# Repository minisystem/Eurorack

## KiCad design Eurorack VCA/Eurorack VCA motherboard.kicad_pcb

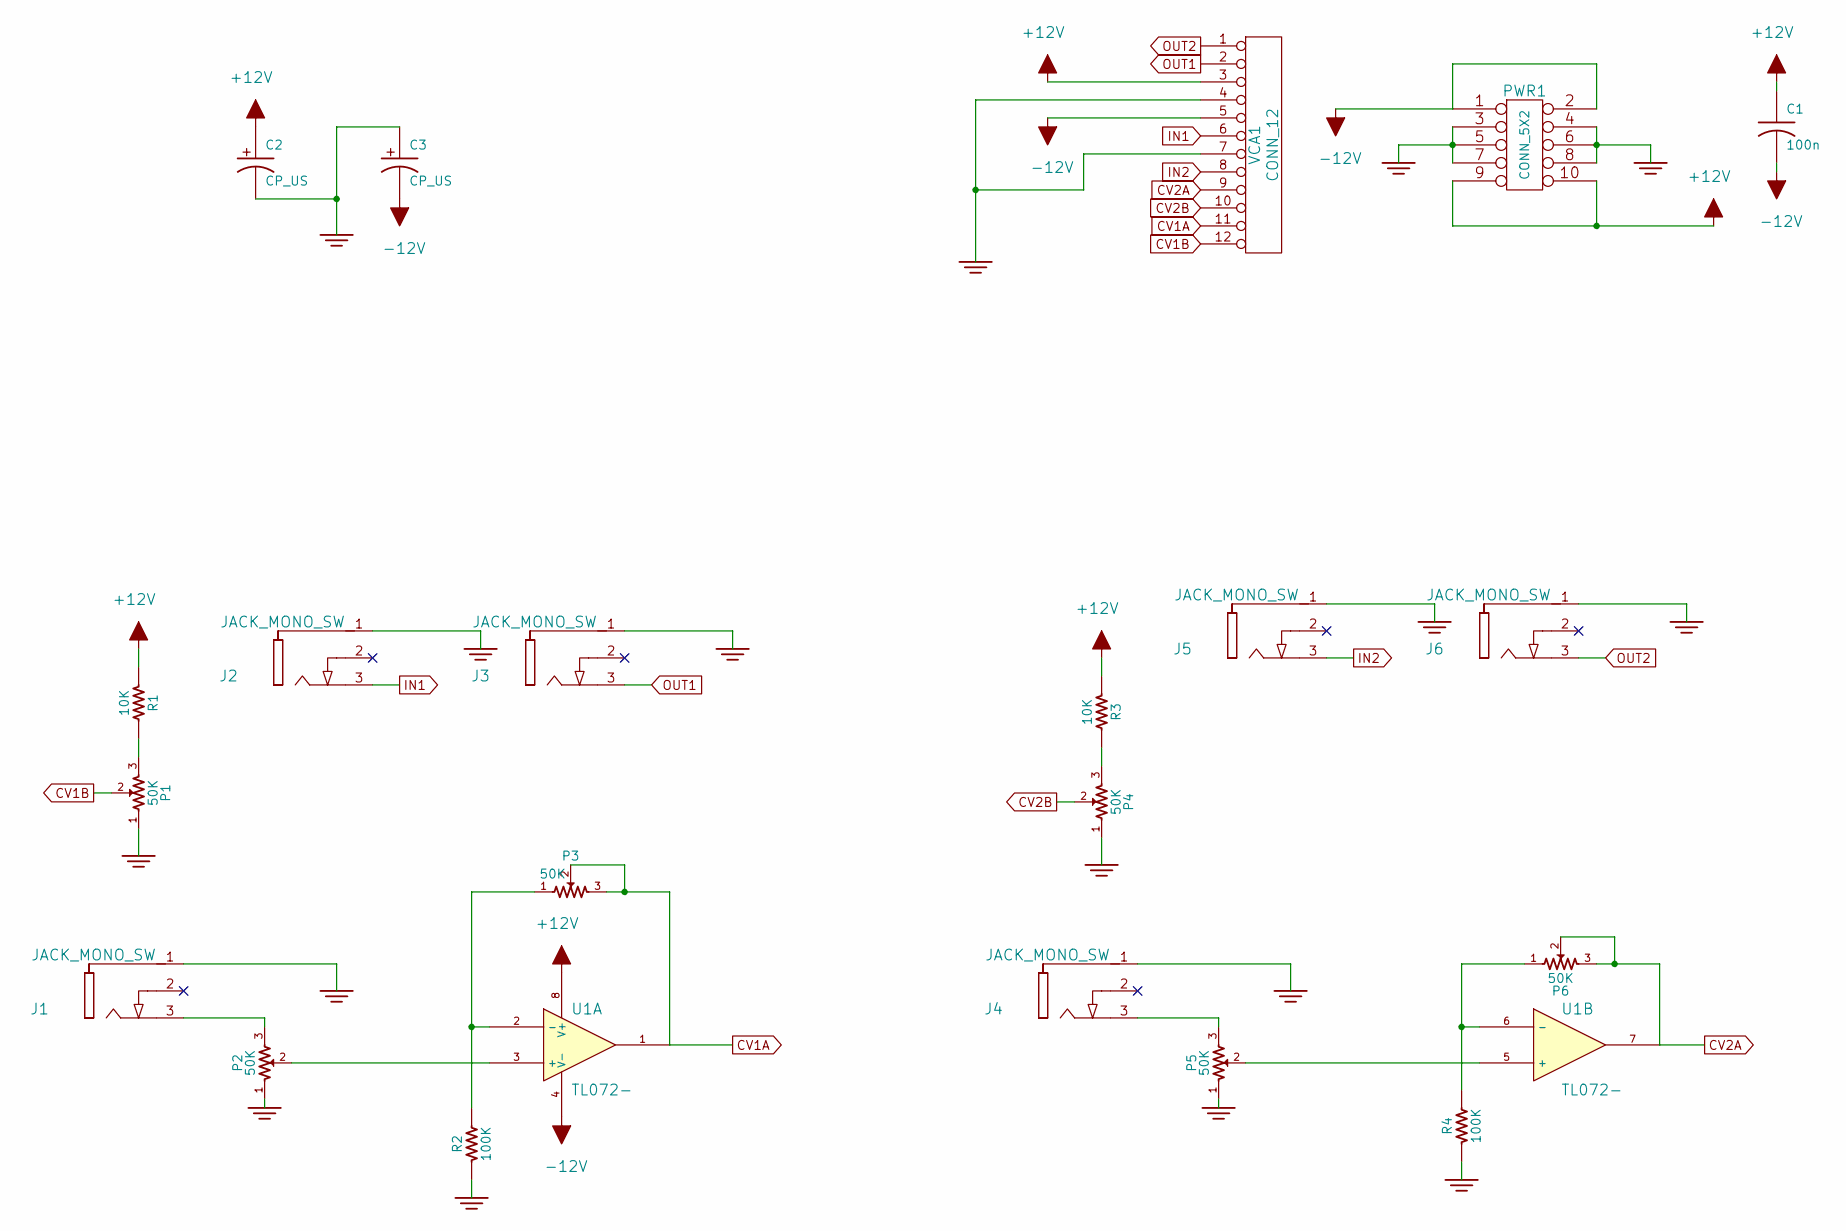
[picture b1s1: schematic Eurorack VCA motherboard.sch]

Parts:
C1: 100n
C2, C3: CP_US
J1, J2, J3, J4, J5, J6: JACK_MONO_SW
P1, P2, P3, P4, P5, P6: 50K
PWR1: CONN_5X2
R1, R3: 10K
R2, R4: 100K
U1: TL072-
VCA1: CONN_12

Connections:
+12V: C1.1, C2.1 (+), PWR1.9, PWR1.10, R1.1, R3.1, U1.8 (V+), VCA1.3
-12V: C1.2, C3.2 (-), PWR1.1, PWR1.2, U1.4 (V-), VCA1.5
CV1A: P3.2, P3.3, U1.1, VCA1.11
CV1B: P1.2, VCA1.12
CV2A: P6.2, P6.3, U1.7, VCA1.9
CV2B: P4.2, VCA1.10
GND: C2.2 (-), C3.1 (+), J1.1, J2.1, J3.1, J4.1, J5.1, J6.1, P1.1, P2.1, P4.1, P5.1, PWR1.3, PWR1.4, PWR1.5, PWR1.6, PWR1.7, PWR1.8, R2.1, R4.1, VCA1.4, VCA1.7
IN1: J2.3, VCA1.6
IN2: J5.3, VCA1.8
unnamed: J1.3, P2.3
unnamed: J4.3, P5.3
unnamed: P1.3, R1.2
unnamed: P2.2, U1.3 (+)
unnamed: P3.1, R2.2, U1.2 (-)
unnamed: P4.3, R3.2
unnamed: P5.2, U1.5 (+)
unnamed: P6.1, R4.2, U1.6 (-)
OUT1: J3.3, VCA1.2
OUT2: J6.3, VCA1.1

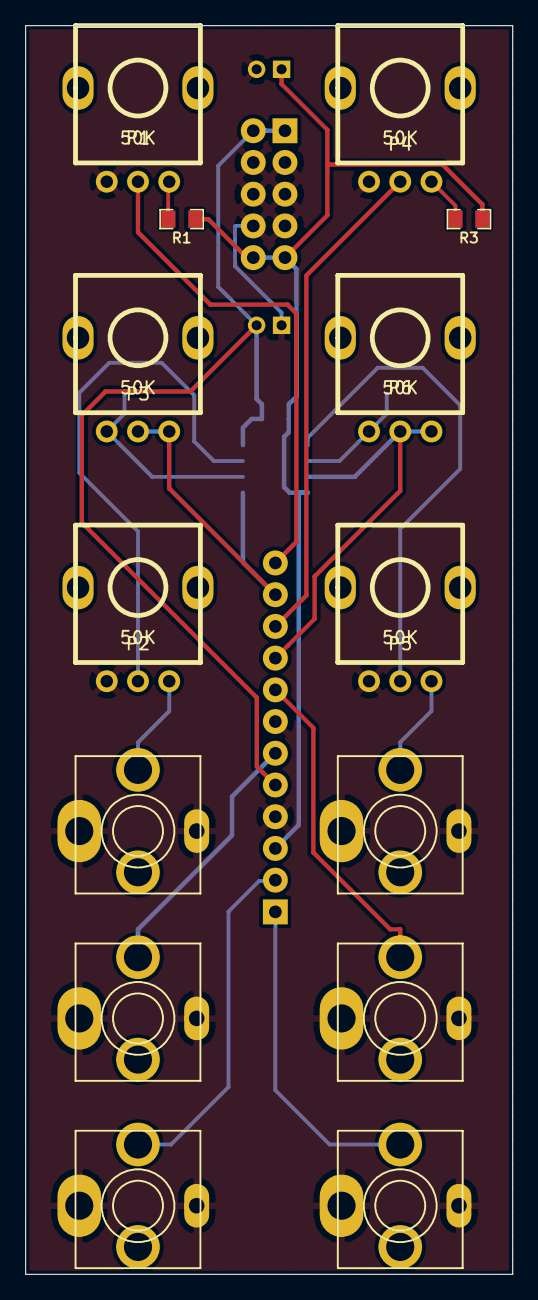
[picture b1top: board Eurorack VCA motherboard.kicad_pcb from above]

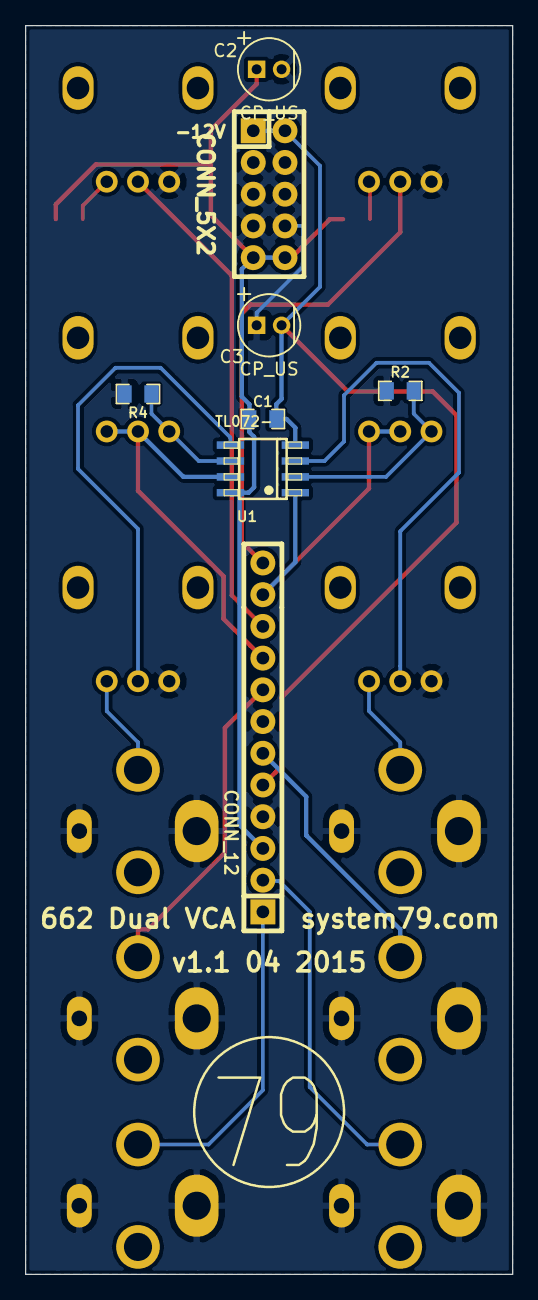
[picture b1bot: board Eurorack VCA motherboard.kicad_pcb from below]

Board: 2 copper layers, 39.0 x 100.0 mm, 23 parts (9 on the bottom side), 19 nets.

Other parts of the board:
system79-logo-12mm: VAL**; system79-logo-12mm

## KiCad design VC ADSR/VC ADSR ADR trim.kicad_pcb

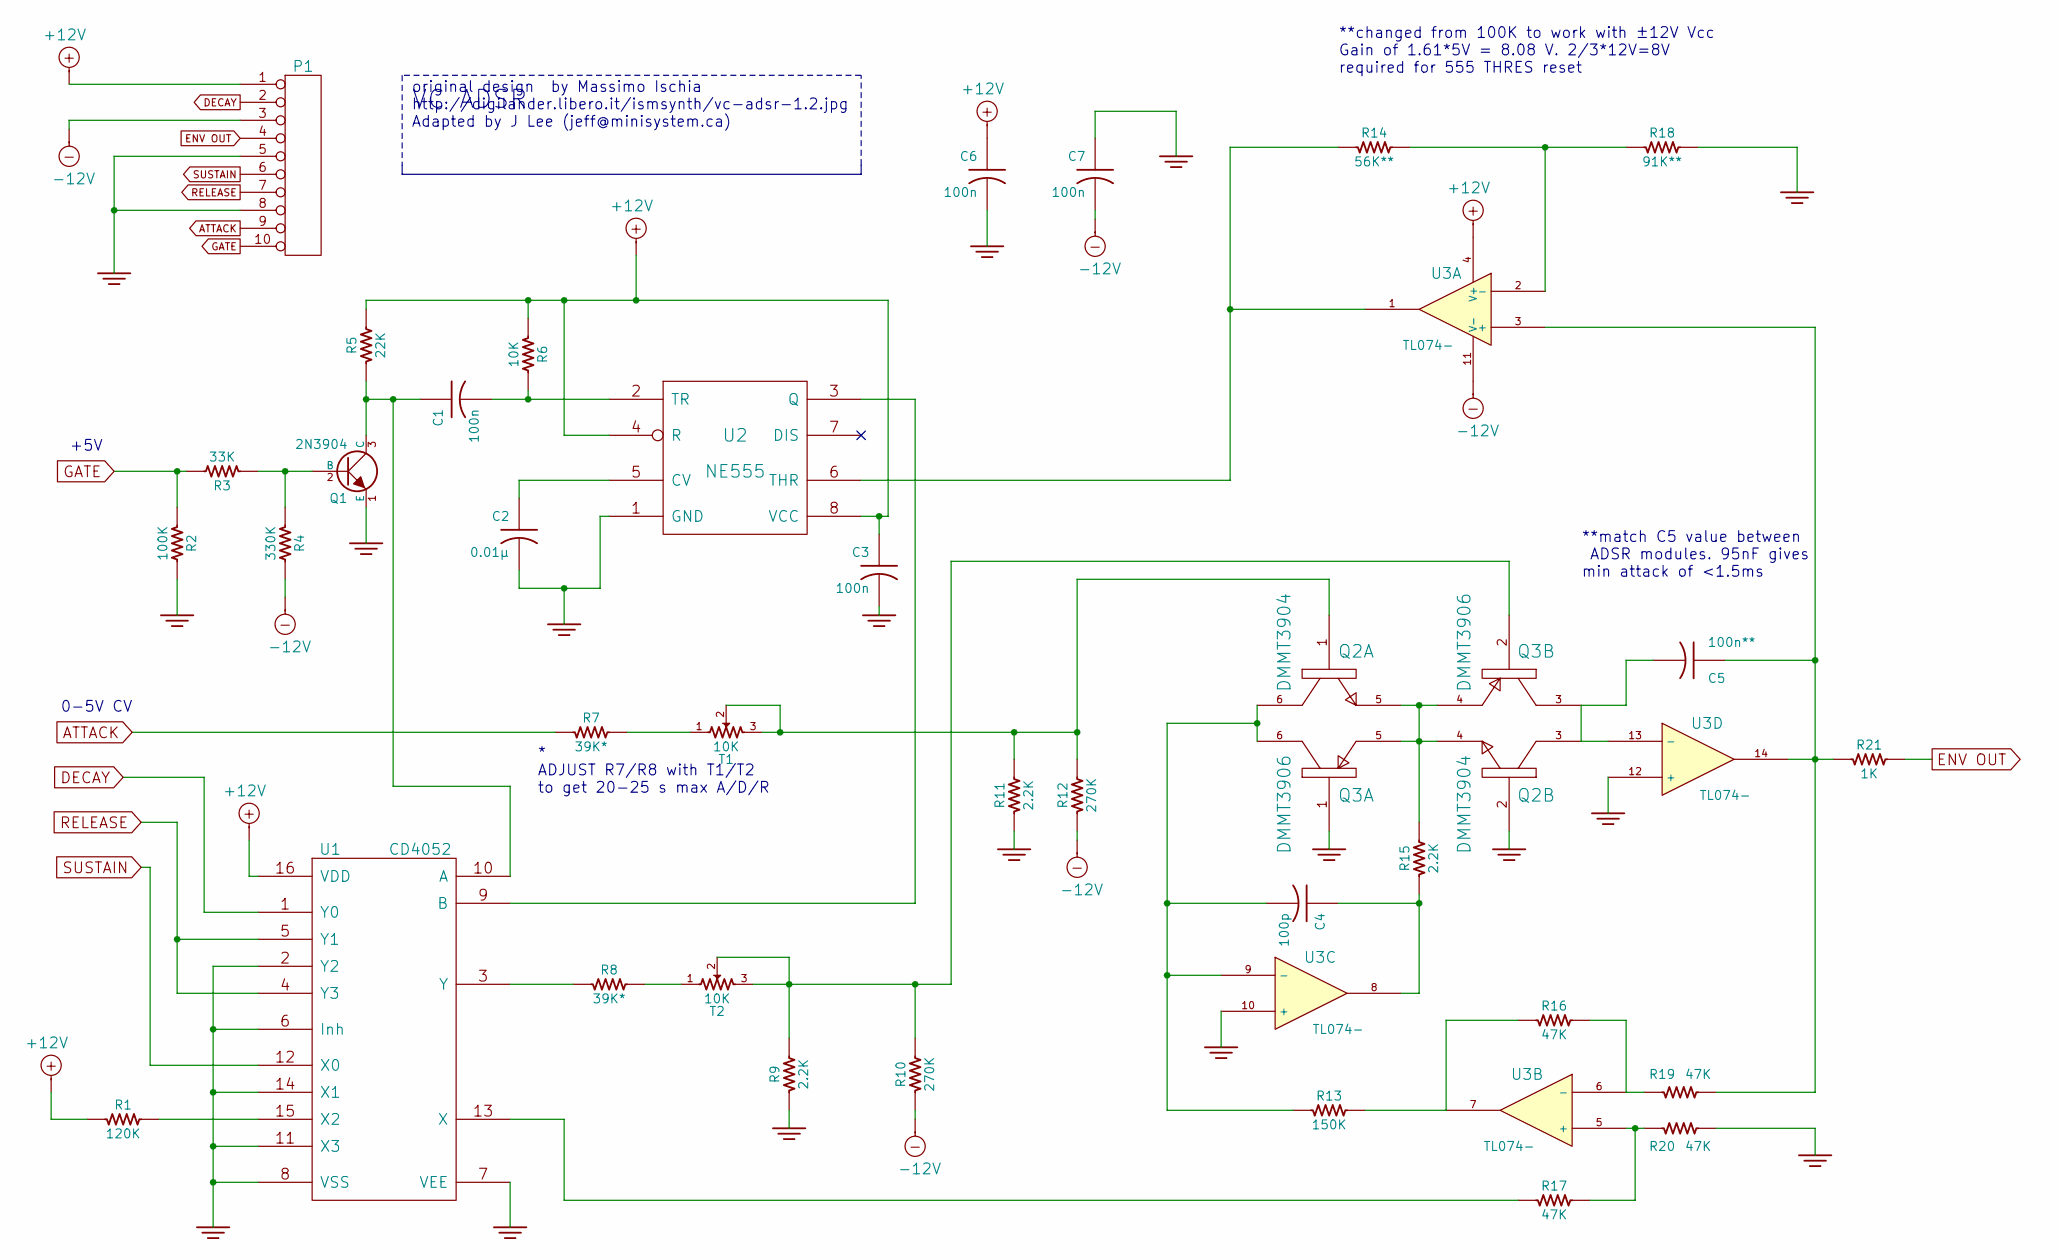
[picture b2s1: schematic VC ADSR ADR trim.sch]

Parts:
C1, C3, C6, C7: 100n
C2: 0.01μ
C4: 100p
C5: 100n**
P1: CONN_10
Q1: 2N3904
Q2: DMMT3904
Q3: DMMT3906
R1: 120K
R2: 100K
R3: 33K
R4: 330K
R5: 22K
R6: 10K
R7, R8: 39K*
R9, R11, R15: 2.2K
R10, R12: 270K
R13: 150K
R14: 56K**
R16, R17, R19, R20: 47K
R18: 91K**
R21: 1K
T1, T2: 10K
U1: CD4052
U2: NE555
U3: TL074-

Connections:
+12V: C3.1, C6.1, P1.1, R1.1, R5.2, R6.1, U1.16 (VDD), U2.4 (R), U2.8 (VCC), U3.4 (V+)
-12V: C7.2, P1.3, R4.2, R10.1, R12.1, U3.11 (V-)
ATTACK: P1.9, R7.1
DECAY: P1.2, U1.1 (Y0)
ENV OUT: P1.4, R21.2
GATE: P1.10, R2.1, R3.2
GND: C2.2, C3.2, C6.2, C7.1, P1.5, P1.8, Q1.1 (E), Q2.2, Q3.1, R2.2, R9.1, R11.1, R18.2, R20.2, U1.2 (Y2), U1.6 (Inh), U1.7 (VEE), U1.8 (VSS), U1.11 (X3), U1.14 (X1), U2.1 (GND), U3.10 (+), U3.12 (+)
unnamed: C1.1, Q1.3 (C), R5.1, U1.10 (A)
unnamed: C1.2, R6.2, U2.2 (TR)
unnamed: C2.1, U2.5 (CV)
unnamed: C4.1, R15.1, U3.8
unnamed: C4.2, Q2.6, Q3.6, R13.1, U3.9 (-)
unnamed: C5.1, R19.2, R21.1, U3.3 (+), U3.14
unnamed: C5.2, Q2.3, Q3.3, U3.13 (-)
unnamed: Q1.2 (B), R3.1, R4.1
unnamed: Q2.1, R11.2, R12.2, T1.2, T1.3
unnamed: Q2.4, Q2.5, Q3.4, Q3.5, R15.2
unnamed: Q3.2, R9.2, R10.2, T2.2, T2.3
unnamed: R1.2, U1.15 (X2)
unnamed: R7.2, T1.1
unnamed: R8.1, U1.3 (Y)
unnamed: R8.2, T2.1
unnamed: R13.2, R16.1, U3.7
unnamed: R14.1, U2.6 (THR), U3.1
unnamed: R14.2, R18.1, U3.2 (-)
unnamed: R16.2, R19.1, U3.6 (-)
unnamed: R17.1, U1.13 (X)
unnamed: R17.2, R20.1, U3.5 (+)
unnamed: U1.9 (B), U2.3 (Q)
RELEASE: P1.7, U1.4 (Y3), U1.5 (Y1)
SUSTAIN: P1.6, U1.12 (X0)

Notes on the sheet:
**changed from 100K to work with ±12V Vcc Gain of 1.61*5V = 8.08 V. 2/3*12V=8V required for 555 THRES reset
* ADJUST R7/R8 with T1/T2 to get 20-25 s max A/D/R
**match C5 value between ADSR modules. 95nF gives min attack of <1.5ms
0-5V CV
+5V
VC ADSR
original design by Massimo Ischia http://digilander.libero.it/ismsynth/vc-adsr-1.2.jpg Adapted by J Lee (jeff@minisystem.ca)

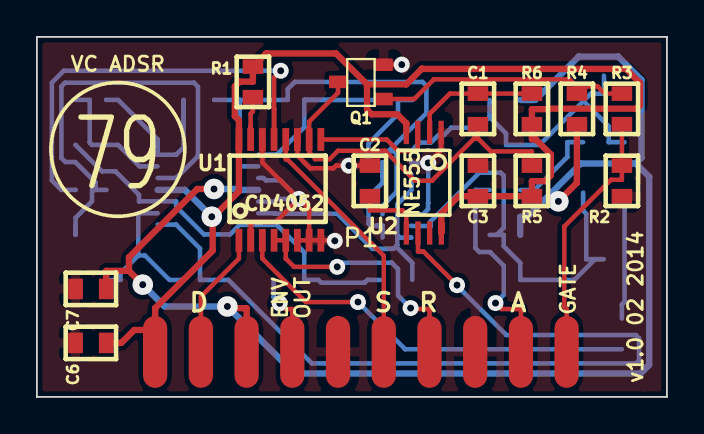
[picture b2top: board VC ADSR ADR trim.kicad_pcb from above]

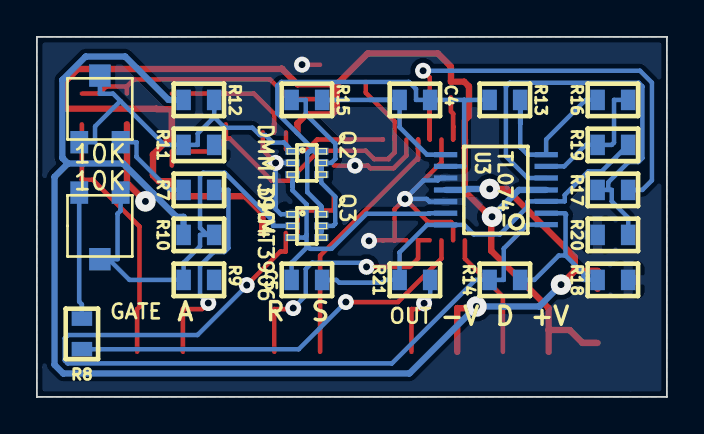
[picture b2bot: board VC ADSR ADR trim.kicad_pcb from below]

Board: 2 copper layers, 35.0 x 20.0 mm, 37 parts (22 on the bottom side), 31 nets.

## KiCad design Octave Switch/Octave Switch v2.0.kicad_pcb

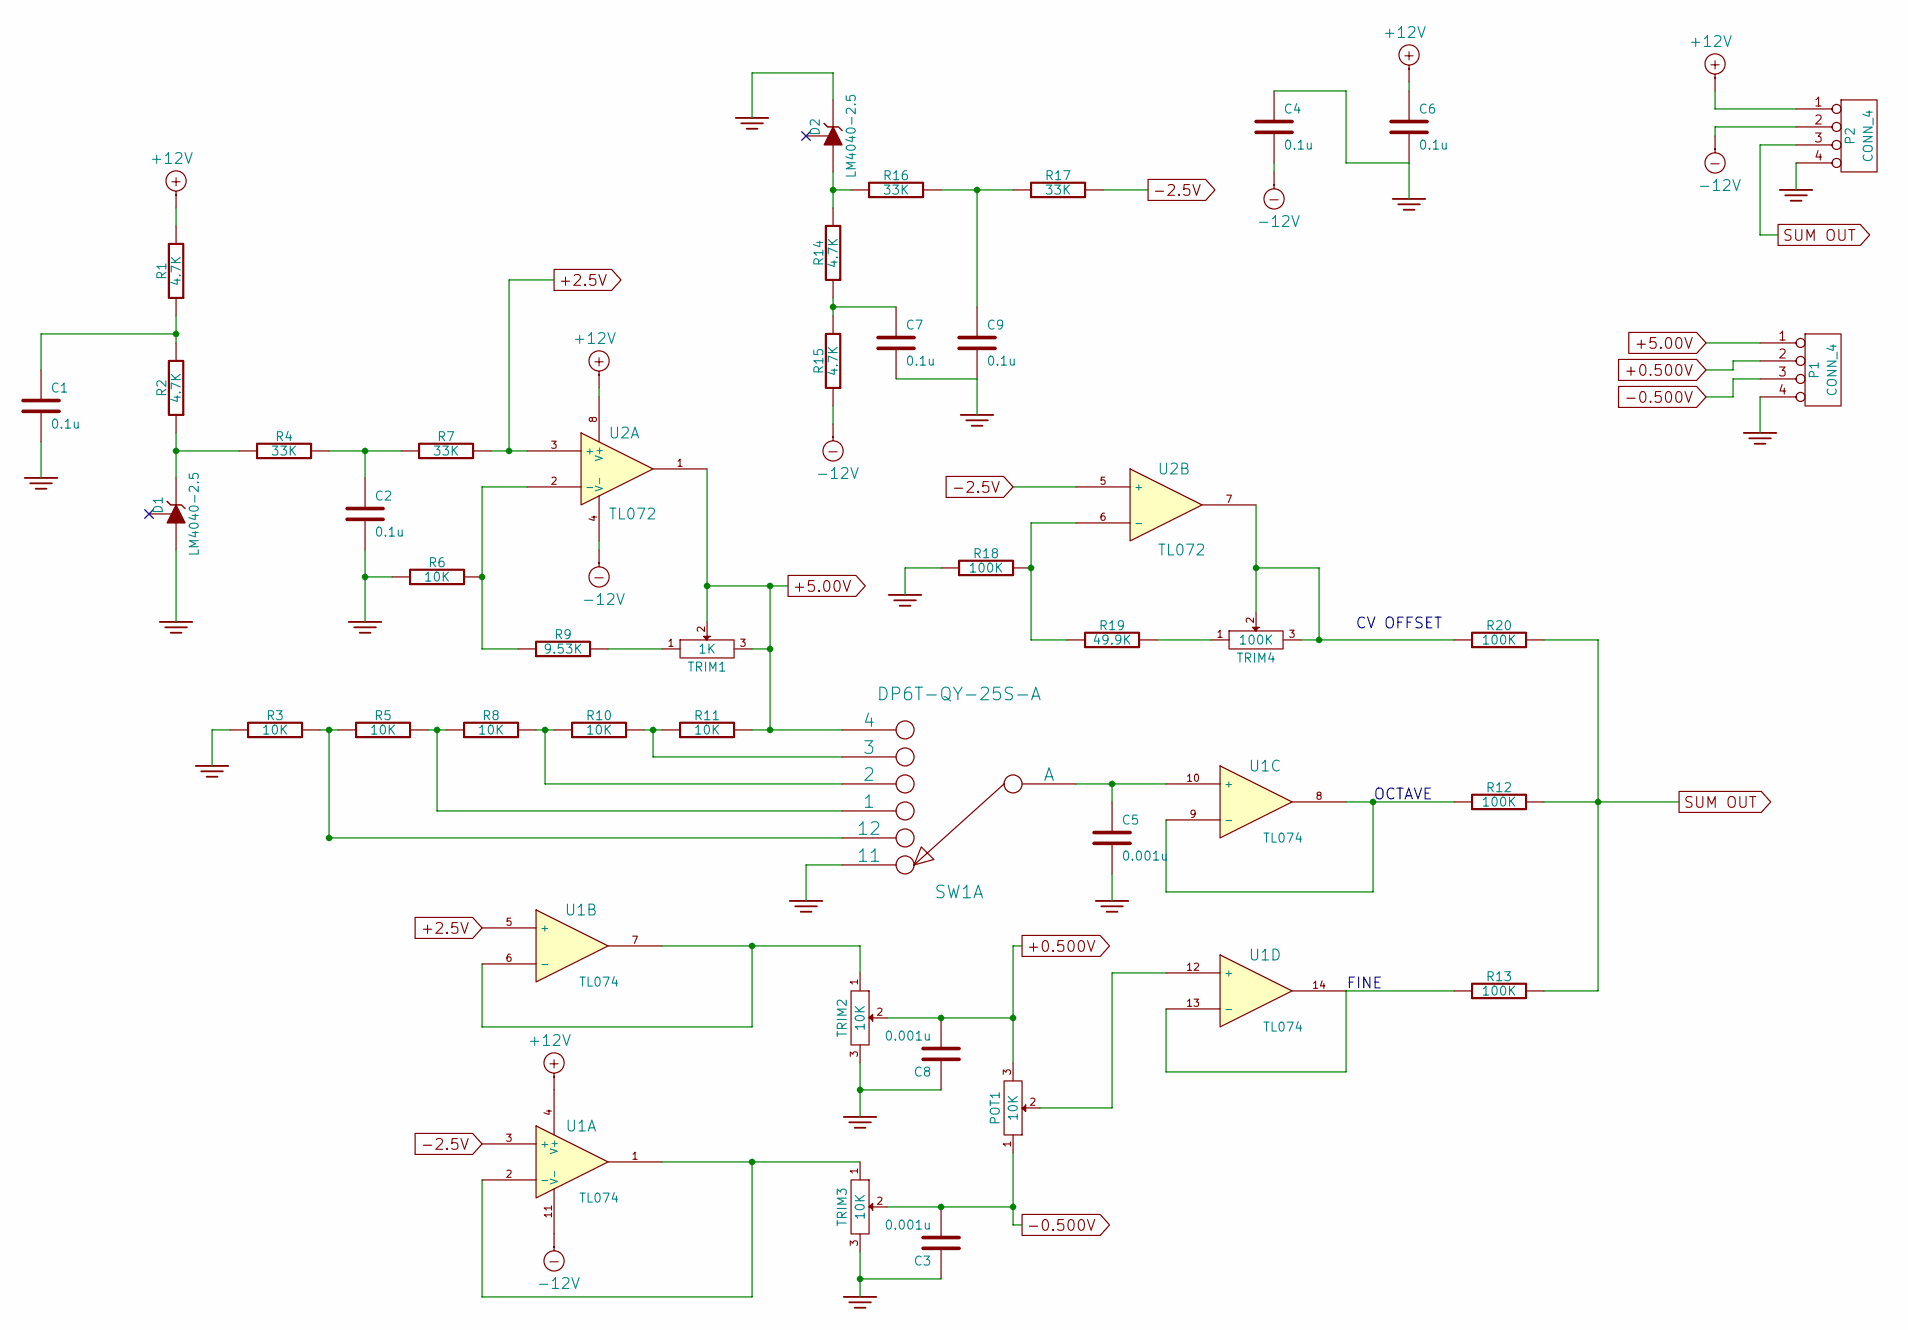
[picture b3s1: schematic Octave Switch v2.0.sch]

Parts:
C1, C2, C4, C6, C7, C9: 0.1u
C3, C5, C8: 0.001u
D1, D2: LM4040-2.5
P1, P2: CONN_4
POT1: 10K
R1, R2, R14, R15: 4.7K
R3, R5, R6, R8, R10, R11: 10K
R4, R7, R16, R17: 33K
R9: 9.53K
R12, R13, R18, R20: 100K
R19: 49.9K
SW1: DP6T-QY-25S-A
TRIM1: 1K
TRIM2, TRIM3: 10K
TRIM4: 100K
U1: TL074
U2: TL072

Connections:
+0.500V: C8.2, P1.2, POT1.3, TRIM2.2
+2.5V: R7.2, U1.5 (+), U2.3 (+)
+5.00V: P1.1, R11.2, SW1.4, TRIM1.2, TRIM1.3, U2.1
+12V: C6.1, P2.1, R1.2, U1.4 (V+), U2.8 (V+)
-0.500V: C3.2, P1.3, POT1.1, TRIM3.2
-2.5V: R17.2, U1.3 (+), U2.5 (+)
-12V: C4.2, P2.2, R15.1, U1.11 (V-), U2.4 (V-)
GND: C1.2, C2.2, C3.1, C4.1, C5.2, C6.2, C7.2, C8.1, C9.2, D1.2 (A), D2.1 (K), P1.4, P2.4, R3.1, R6.1, R18.1, SW1.11, TRIM2.3, TRIM3.3
unnamed: R13.1, U1.13 (-), U1.14
unnamed: R12.1, U1.8, U1.9 (-)
unnamed: R3.2, R5.1, SW1.12
unnamed: R5.2, R8.1, SW1.1
unnamed: D1.1 (K), R2.1, R4.1
unnamed: C1.1, R1.1, R2.2
unnamed: R9.2, TRIM1.1
unnamed: C2.1, R4.2, R7.1
unnamed: R8.2, R10.1, SW1.2
unnamed: R10.2, R11.1, SW1.3
unnamed: R20.1, TRIM4.2, TRIM4.3, U2.7
unnamed: R19.2, TRIM4.1
unnamed: TRIM2.1, U1.6 (-), U1.7
unnamed: TRIM3.1, U1.1, U1.2 (-)
unnamed: D2.2 (A), R14.2, R16.1
unnamed: C9.1, R16.2, R17.1
unnamed: POT1.2, U1.12 (+)
unnamed: C5.1, SW1.A, U1.10 (+)
unnamed: C7.1, R14.1, R15.2
unnamed: R6.2, R9.1, U2.2 (-)
unnamed: R18.2, R19.1, U2.6 (-)
SUM OUT: P2.3, R12.2, R13.2, R20.2

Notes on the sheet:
FINE
OCTAVE
CV OFFSET

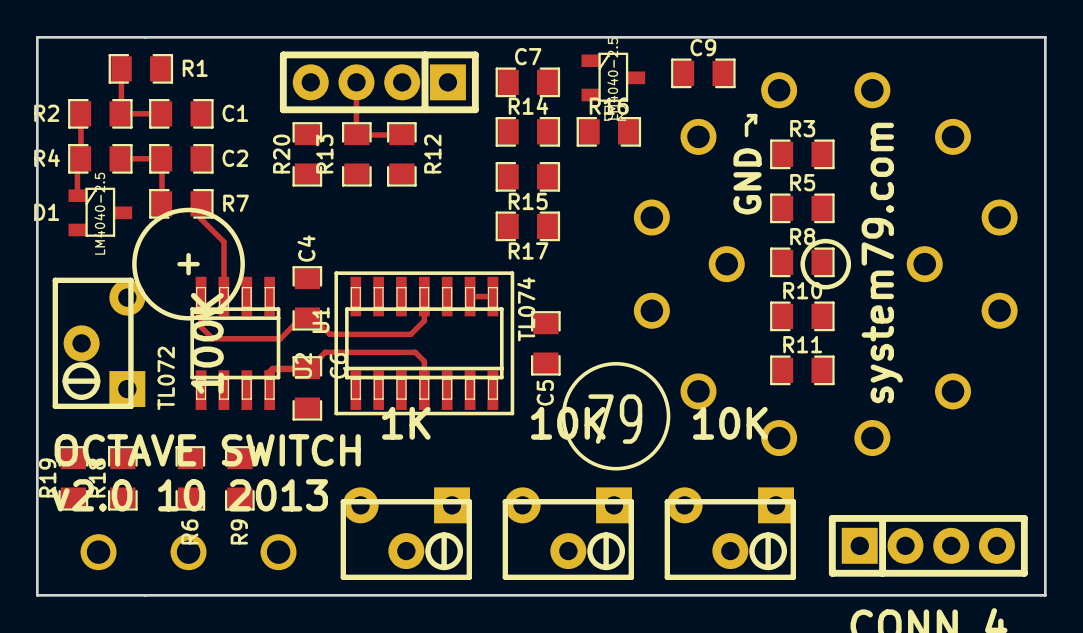
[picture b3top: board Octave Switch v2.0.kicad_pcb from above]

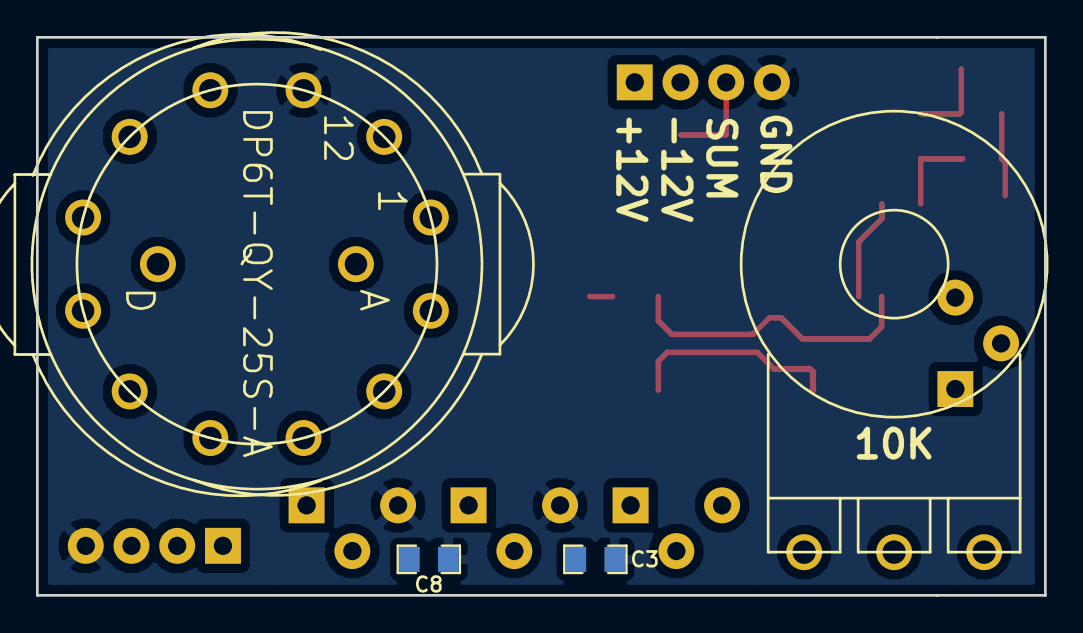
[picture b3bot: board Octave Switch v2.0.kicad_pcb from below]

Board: 2 copper layers, 56.0 x 31.0 mm, 41 parts (4 on the bottom side), 30 nets.

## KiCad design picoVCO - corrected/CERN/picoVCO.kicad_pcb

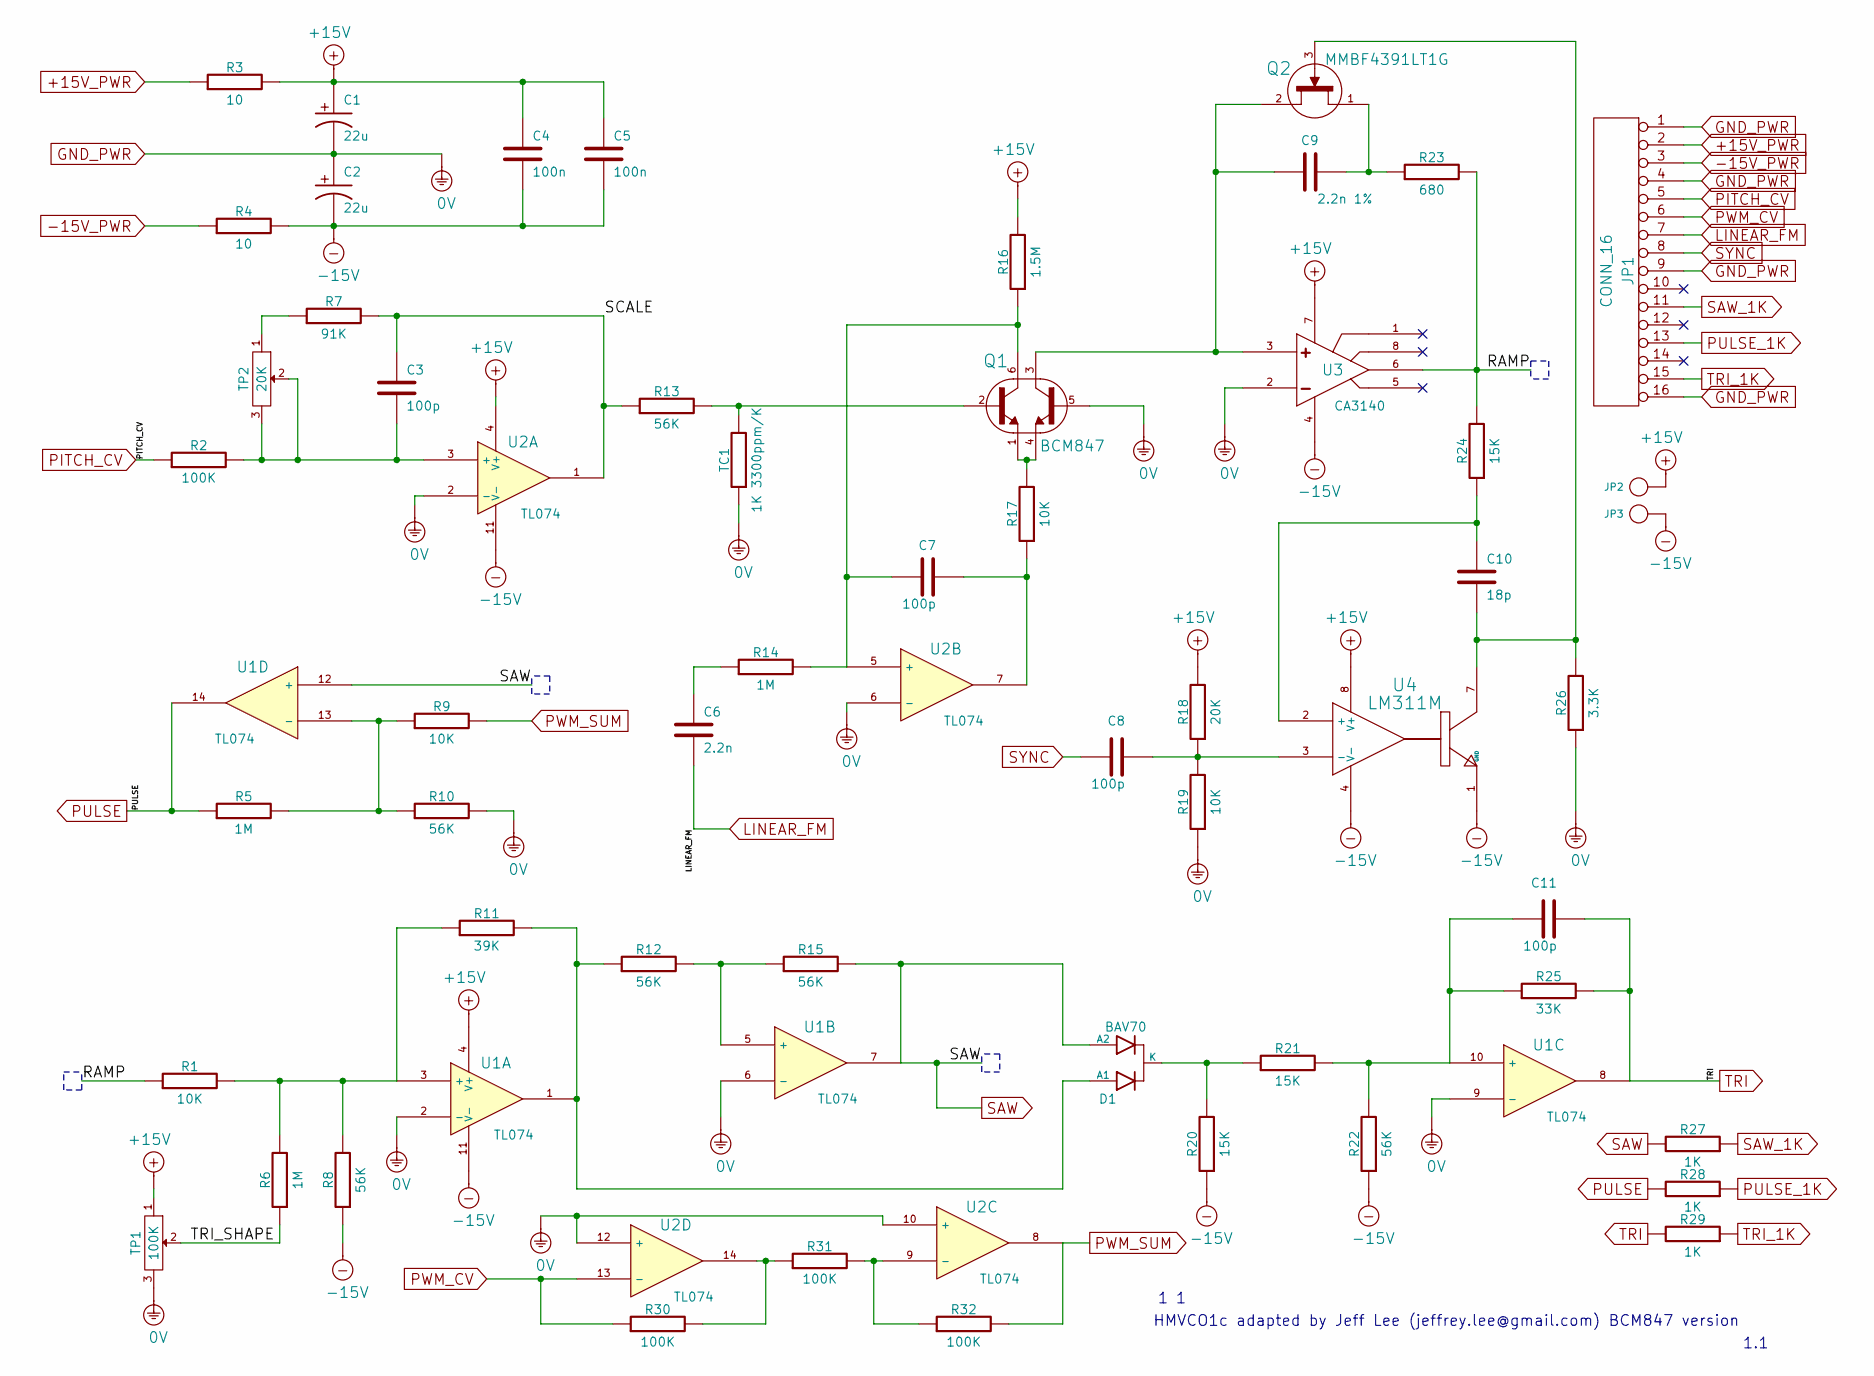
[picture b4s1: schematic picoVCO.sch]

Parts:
C1, C2: 22u; Digikey 493-3949-1-ND
C3, C7, C8, C11: 100p; Digikey 399-1122-1-ND
C4, C5: 100n; Digikey 478-1395-1-ND
C6: 2.2n; Digikey 445-1332-1-ND
C9: 2.2n 1%; Digikey 399-9198-1-ND
C10: 18p; Digikey 399-1112-1-ND
D1: BAV70; Digikey BAV70-V-GS08CT-ND
JP1: CONN_16
JP2, JP3: CONN_1
Q1: BCM847; Digikey 568-6098-1-ND
Q2: MMBF4391LT1G; Digikey MMBF4391LT1GOSCT-ND
R1, R9, R17, R19: 10K; Digikey P10.0KCCT-ND
R2, R30, R31, R32: 100K; Digikey P100KCCT-ND
R3, R4: 10; Digikey RNCP0805FTD10R0CT-ND
R5, R6, R14: 1M; Digikey P1.00MCCT-ND
R7: 91K; Digikey P91.0KCCT-ND
R8, R10, R12, R13, R15, R22: 56K; Digikey P56.0KCCT-ND
R11: 39K; Digikey P39.0KCCT-ND
R16: 1.5M; Digikey P1.50MCCT-ND
R18: 20K; Digikey P20.0KCCT-ND
R20, R21, R24: 15K; Digikey P15.0KCCT-ND
R23: 680; Digikey P680CCT-ND
R25: 33K; Digikey P33.0KCCT-ND
R26: 3.3K; Digikey P3.30KCCT-ND
R27, R28, R29: 1K; Digikey P1.00KCCT-ND
TC1: 1K 3300ppm/K; Digikey P1.0KCDCT-ND
TP1: 100K; Digikey SM-42TA104CT-ND
TP2: 20K; Digikey SM-42TA203CT-ND
U1, U2: TL074; Digikey 296-1283-1-ND
U3: CA3140; Digikey CA3140AMZ-ND
U4: LM311M; Digikey 296-1388-1-ND

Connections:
+15V: C1.1 (+), C4.1, C5.1, JP2.1, R3.2, R16.2, R18.2, TP1.1, U1.4 (V+), U2.4 (V+), U3.7 (V+), U4.8 (V+)
+15V_PWR: JP1.2, R3.1
-15V: C2.2 (-), C4.2, C5.2, JP3.1, R4.2, R8.1, R20.1, R22.1, U1.11 (V-), U2.11 (V-), U3.4 (V-), U4.1 (GND), U4.4 (V-)
-15V_PWR: JP1.3, R4.1
/RAMP: R1.1, R23.2, R24.2, U3.6 (OUTPUT)
/SCALE: C3.1, R7.2, R13.1, U2.1
/TRI_SHAPE: R6.1, TP1.2
GND_PWR: C1.2 (-), C2.1 (+), JP1.1, JP1.4, JP1.9, JP1.16, Q1.5 (B2), R10.2, R19.1, R26.1, TC1.1, TP1.3, U1.2 (-), U1.6 (-), U1.9 (-), U2.2 (-), U2.6 (-), U2.10 (+), U2.12 (+), U3.2 (INVERTING)
LINEAR_FM: C6.2, JP1.7
unnamed: C8.2, R18.1, R19.2, U4.3 (-)
unnamed: Q1.1 (E1), Q1.4 (E2), R17.2
unnamed: C7.1, Q1.6 (C1), R14.2, R16.1, U2.5 (+)
unnamed: C6.1, R14.1
unnamed: R1.2, R6.2, R8.2, R11.1, U1.3 (+)
unnamed: R12.2, R15.1, U1.5 (+)
unnamed: R31.2, R32.1, U2.9 (-)
unnamed: R30.2, R31.1, U2.14
unnamed: R7.1, TP2.1
unnamed: Q1.2 (B1), R13.2, TC1.2
unnamed: C9.2, Q2.1 (D), R23.1
unnamed: C7.2, R17.1, U2.7
unnamed: C10.2, Q2.3 (G), R26.2, U4.7
unnamed: C9.1, Q1.3 (C2), Q2.2 (S), U3.3 (NON)
unnamed: C3.2, R2.2, TP2.2, TP2.3, U2.3 (+)
unnamed: D1.3 (K), R20.2, R21.1
unnamed: C10.1, R24.1, U4.2 (+)
unnamed: C11.1, R21.2, R22.2, R25.1, U1.10 (+)
unnamed: D1.1 (A1), R11.2, R12.1, U1.1
unnamed: R5.2, R9.1, R10.1, U1.13 (-)
PITCH_CV: JP1.5, R2.1
PULSE: R5.1, R28.2, U1.14
PULSE_1K: JP1.13, R28.1
PWM_CV: JP1.6, R30.1, U2.13 (-)
PWM_SUM: R9.2, R32.2, U2.8
SAW: D1.2 (A2), R15.2, R27.2, U1.7, U1.12 (+)
SAW_1K: JP1.11, R27.1
SYNC: C8.1, JP1.8
TRI: C11.2, R25.2, R29.2, U1.8
TRI_1K: JP1.15, R29.1

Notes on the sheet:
1.1
HMVCO1c adapted by Jeff Lee (jeffrey.lee@gmail.com) BCM847 version

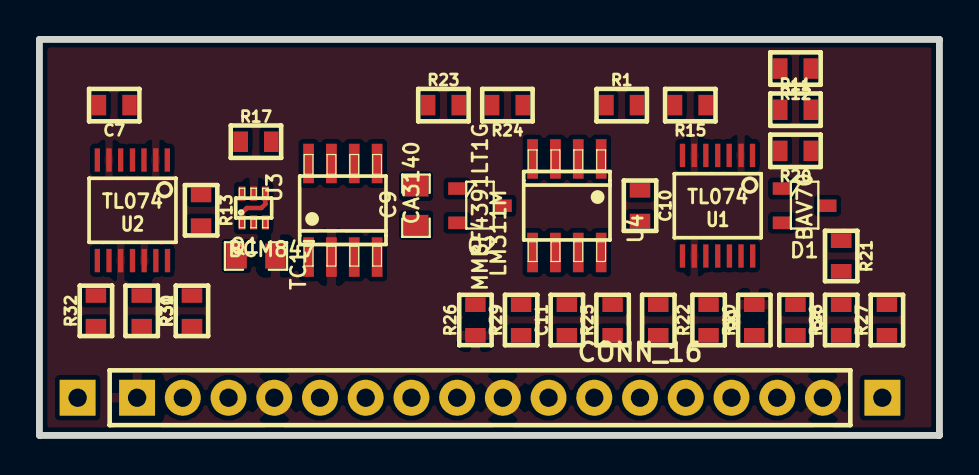
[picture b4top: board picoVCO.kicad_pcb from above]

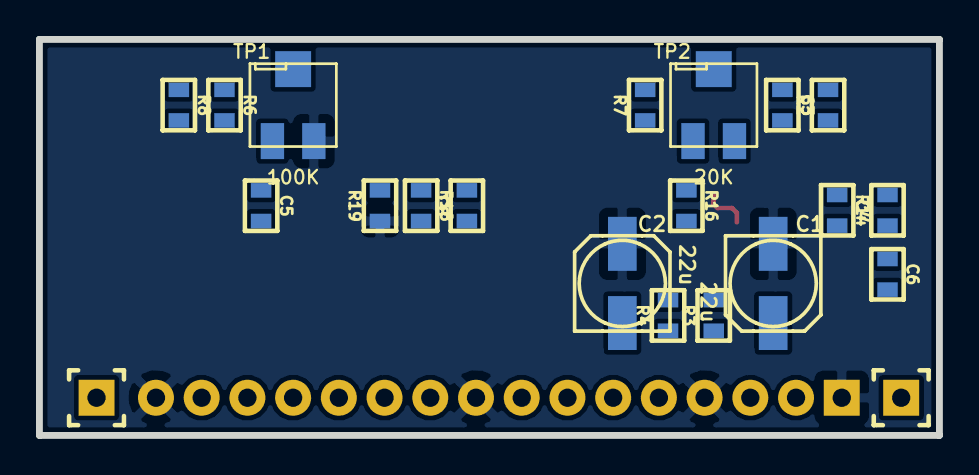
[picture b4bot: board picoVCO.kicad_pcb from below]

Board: 2 copper layers, 50.0 x 22.0 mm, 56 parts (21 on the bottom side), 39 nets.

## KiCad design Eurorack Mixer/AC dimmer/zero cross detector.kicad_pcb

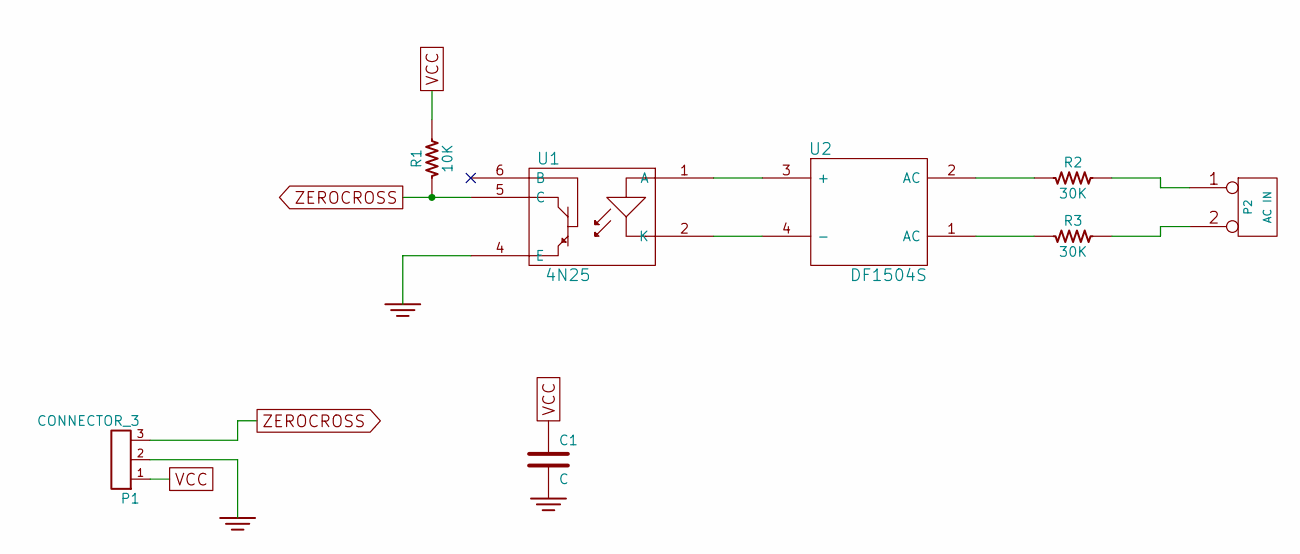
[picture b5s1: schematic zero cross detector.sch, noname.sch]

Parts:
C1: C
P1: CONNECTOR_3
P2: AC IN
R1: 10K
R2, R3: 30K
U1: 4N25
U2: DF1504S

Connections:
GND: C1.2, P1.2, U1.4 (E)
unnamed: P2.2 (PM), R3.2
unnamed: P2.1, R2.2
unnamed: R3.1, U2.1 (AC)
unnamed: R2.1, U2.2 (AC)
unnamed: U1.1 (A), U2.3 (+)
unnamed: U1.2 (K), U2.4 (-)
VCC: C1.1, P1.1, R1.2
ZEROCROSS: P1.3, R1.1, U1.5 (C)

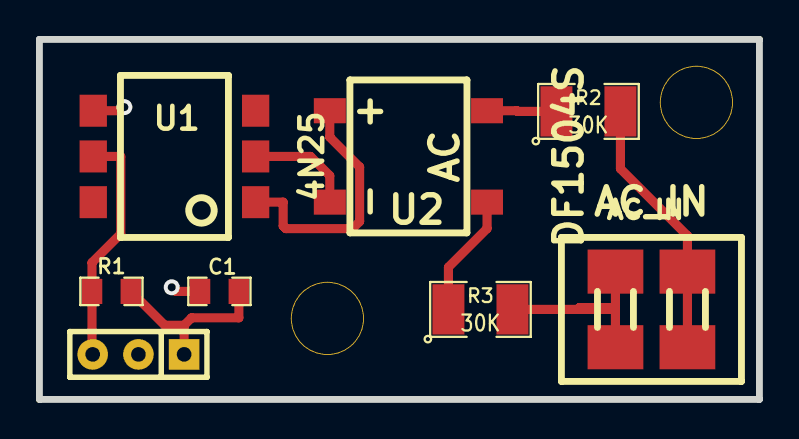
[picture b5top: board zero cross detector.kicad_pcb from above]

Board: 2 copper layers, 40.0 x 20.0 mm, 11 parts (1 on the bottom side), 9 nets.

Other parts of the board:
DRILL 0.156in, DRILL 0.156in#2: VAL**; DRILL
LeuWebb: VAL**; LeuWebb2
